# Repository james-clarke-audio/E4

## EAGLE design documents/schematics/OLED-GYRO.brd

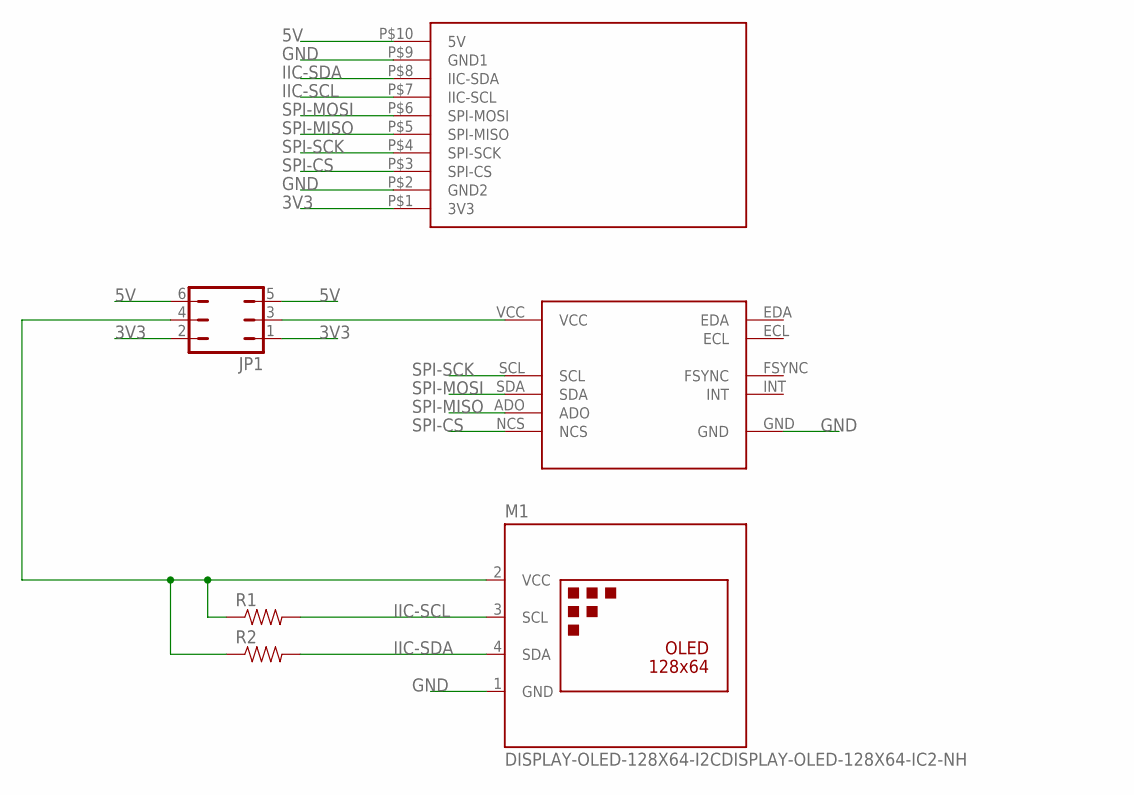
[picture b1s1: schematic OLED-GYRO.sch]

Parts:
JP1: JP3Q
M1: DISPLAY-OLED-128X64-I2CDISPLAY-OLED-128X64-IC2-NH; DISPLAY-OLED-128X64-I2C_NH
R1, R2: RESISTORPTH-1/4W; AXIAL-0.4
U$1: E4_SPI-IIC
U$2: MPU-9250/6500; MPU9265

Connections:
3V3: JP1.1, JP1.2, U$1.P$1 (3V3)
5V: JP1.5, JP1.6, U$1.P$10 (5V)
GND: M1.1 (GND), U$1.P$2 (GND2), U$1.P$9 (GND1), U$2.GND
IIC-SCL: M1.3 (SCL), R1.P$2 (2), U$1.P$7 (IIC-SCL)
IIC-SDA: M1.4 (SDA), R2.P$2 (2), U$1.P$8 (IIC-SDA)
unnamed: JP1.3, U$2.VCC
unnamed: JP1.4, M1.2 (VCC), R1.P$1 (1), R2.P$1 (1)
SPI-CS: U$1.P$3 (SPI-CS), U$2.NCS
SPI-MISO: U$1.P$5 (SPI-MISO), U$2.ADO
SPI-MOSI: U$1.P$6 (SPI-MOSI), U$2.SDA
SPI-SCK: U$1.P$4 (SPI-SCK), U$2.SCL

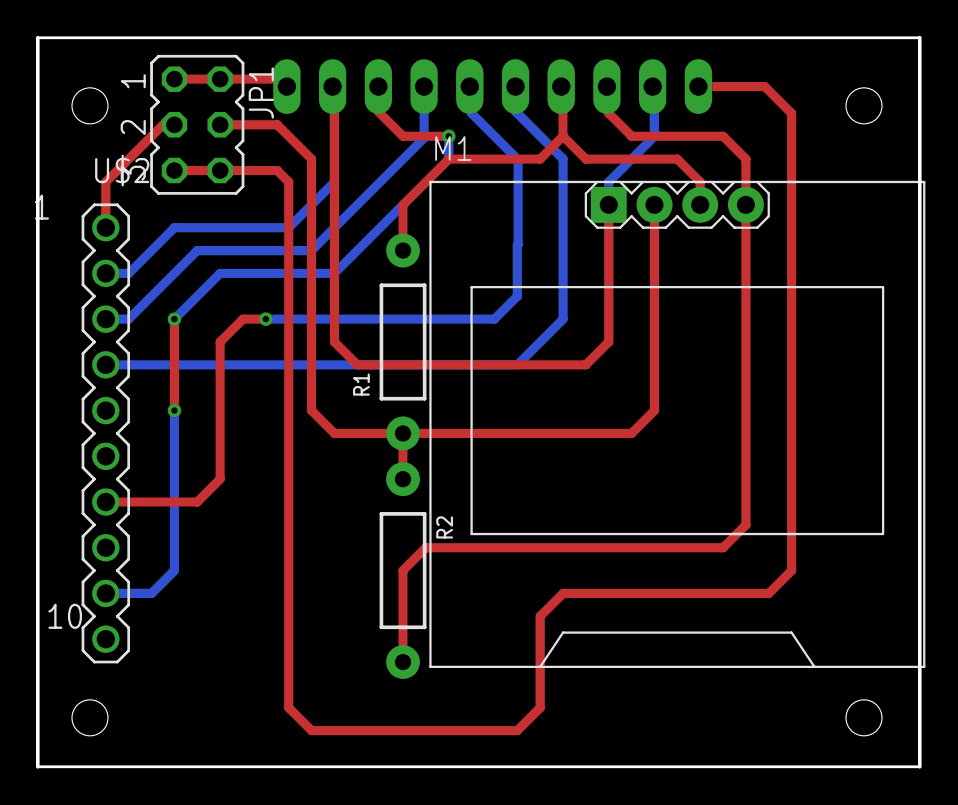
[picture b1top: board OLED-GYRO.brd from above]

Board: 2 copper layers, 49.0 x 40.5 mm, 6 parts (0 on the bottom side), 11 nets.

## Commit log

2024-01-21 Committing
2024-05-07 Add Documents to repo
    Add base documents to repository
2024-05-07 rollback and update
2024-05-07 Display moved to class def
2024-05-07 added .DS_Store to gitignore
2024-05-16 Migration of code
    Migrated OLED (display) and I2C to lib folder and converted to c++ class
2024-05-17 Directory cleanup
    Cleanup directories and prepare for next hardware modules
2024-05-23 Encoder Modules
    Need to update
2024-05-23 Update encoder.cpp
    update
2024-05-23 Encoders phase 1 complete
    Encoders working. Created new timer object and passed in
2024-05-24 Added print float and integer functions
    Added print float and integer functions
2024-06-02 new OLED board
    Added IIC eeprom to the OLED / Gyro board

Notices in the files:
parts and their libraries:
SparkFun: Licensing: CC v3.0 Share-Alike You are welcome to use this library for commercial purposes.
